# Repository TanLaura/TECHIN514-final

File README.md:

# TECHIN514-final

## Daily Habit Tracker
The device tracks the number of task completed (chips in the collector/sensing device) and show the progress with the stepper gauge needle. The LED light can be on the scale of red to green based on percentage of completion. It relies on the load cell and amplifier to calculate the number of chips of completed tasks and completion rate based on the set goal of the day. The stepper motor gauge and LED will display the progress. The display device also have the option to set the goals.

## Sensor device
The sensor device looks like a bowl overall. There is a load cell and amplifier that read the weight and translate it to voltage. It calculates the percentage of task completion and send the data to display device for further information display.

## Display Device
The outer shape can be varied based on the final PCB shape and size. The diplay has a stepper motor gauge and LED light both shows the completion rate of the task in different forms. It has a reset button and button to adjust the goal of the day.

## Device Communicatioin 

### Component Lists
- [Seeduino ESP32C3](Datasheets/Seeduino ESP32c3.pdf)
- [Load cell](https://www.adafruit.com/product/4541#description): The load cell seems to only have a webpage with product details instead of a datasheet.
- [HX711](Datasheets/adafruit-hx711-24-bit-adc.pdf)
- [Stepper Motor Gauage](Datasheets/stepd-01-data-sheet-1143075.pdf)
- [LED WS2812](Datasheets/WS2812.pdf)

### Potential Component to Add after Discussion 
- A small display screen
- The reset button (and its form)
- A charging circuit?
- Sleep mode?

These are all questions I want to go over with the instruction team to finalize the component list and structure.

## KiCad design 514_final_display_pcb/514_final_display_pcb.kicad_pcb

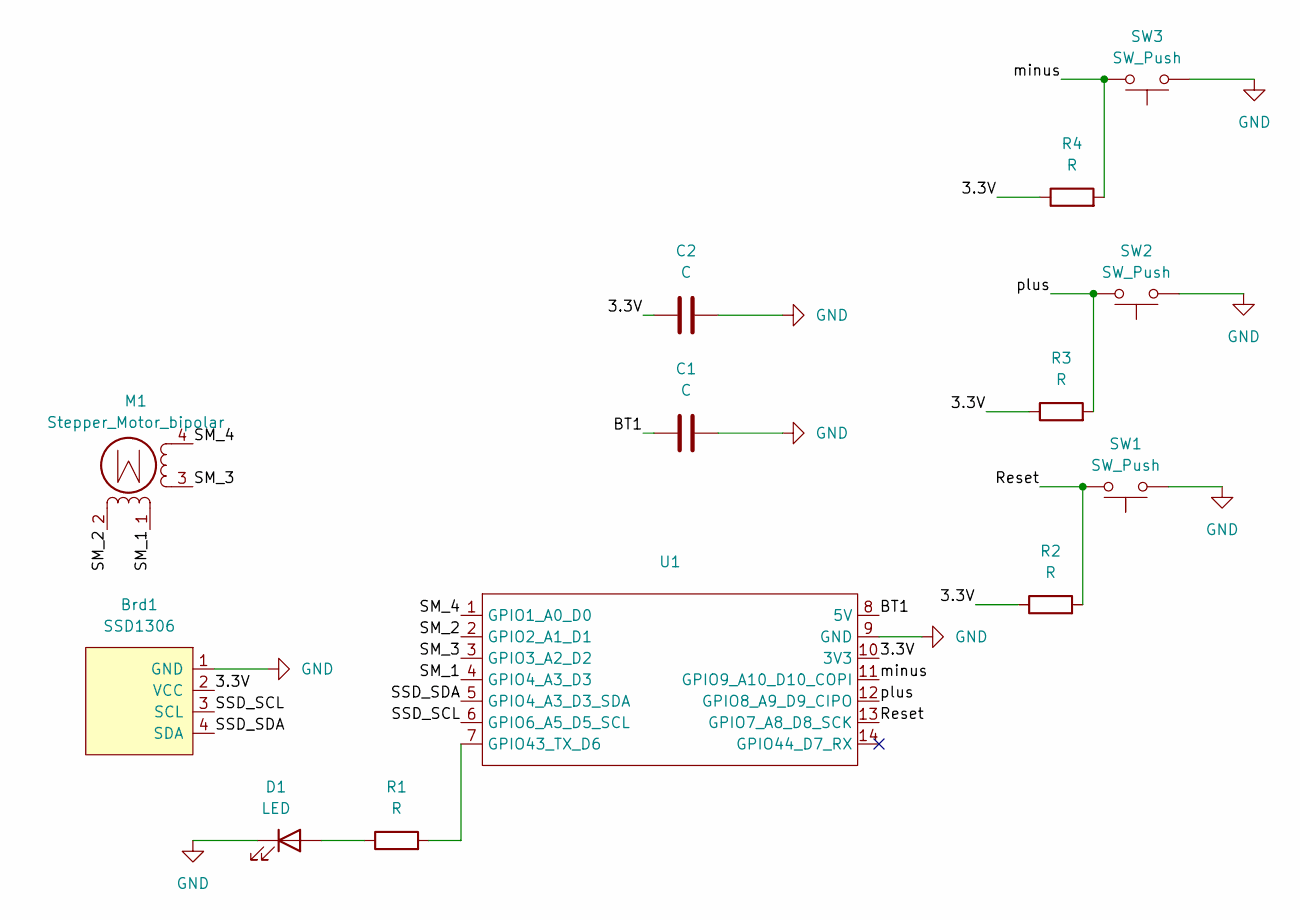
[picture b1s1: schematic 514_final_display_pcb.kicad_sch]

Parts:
Brd1: SSD1306; 128x64OLED
C1, C2: C; C_0805_2012Metric_Pad1.18x1.45mm_HandSolder
D1: LED; LED_D5.0mm
M1: Stepper_Motor_bipolar; x27_stepper_two_holes
R1, R2, R3, R4: R; R_0805_2012Metric_Pad1.20x1.40mm_HandSolder
SW1, SW2, SW3: SW_Push; SW_PUSH_6mm
U1: XIAO_ESP32_SENSE

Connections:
/3.3V: Brd1.2 (VCC), C2.1, R2.1, R3.1, R4.1, U1.10 (3V3)
/BT1: C1.1, U1.8 (5V)
/Reset: R2.2, SW1.2, U1.13 (GPIO7_A8_D8_SCK)
/SM_1: M1.1, U1.4 (GPIO4_A3_D3)
/SM_2: M1.2 (-), U1.2 (GPIO2_A1_D1)
/SM_3: M1.3, U1.3 (GPIO3_A2_D2)
/SM_4: M1.4, U1.1 (GPIO1_A0_D0)
/SSD_SCL: Brd1.3 (SCL), U1.6 (GPIO6_A5_D5_SCL)
/SSD_SDA: Brd1.4 (SDA), U1.5 (GPIO4_A3_D3_SDA)
/minus: R4.2, SW3.2, U1.11 (GPIO9_A10_D10_COPI)
/plus: R3.2, SW2.2, U1.12 (GPIO8_A9_D9_CIPO)
GND: Brd1.1 (GND), C1.2, C2.2, D1.1 (K), SW1.1, SW2.1, SW3.1, U1.9 (GND)
unnamed: D1.2 (A), R1.1
unnamed: R1.2, U1.7 (GPIO43_TX_D6)

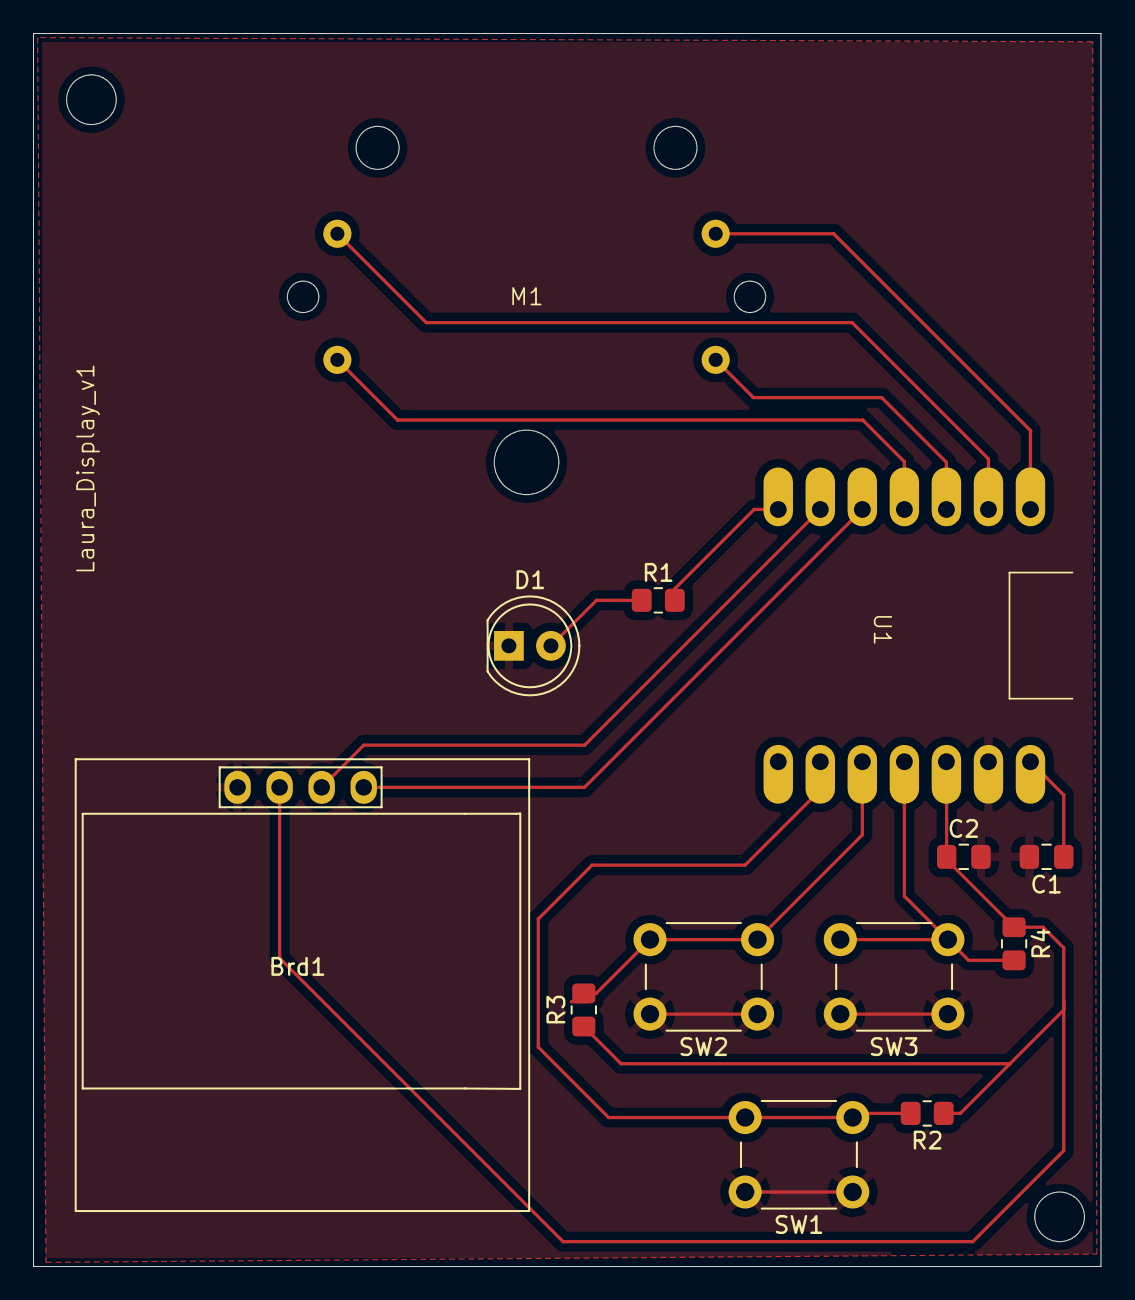
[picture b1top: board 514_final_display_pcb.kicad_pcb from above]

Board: 2 copper layers, 64.5 x 74.5 mm, 13 parts (0 on the bottom side), 14 nets.

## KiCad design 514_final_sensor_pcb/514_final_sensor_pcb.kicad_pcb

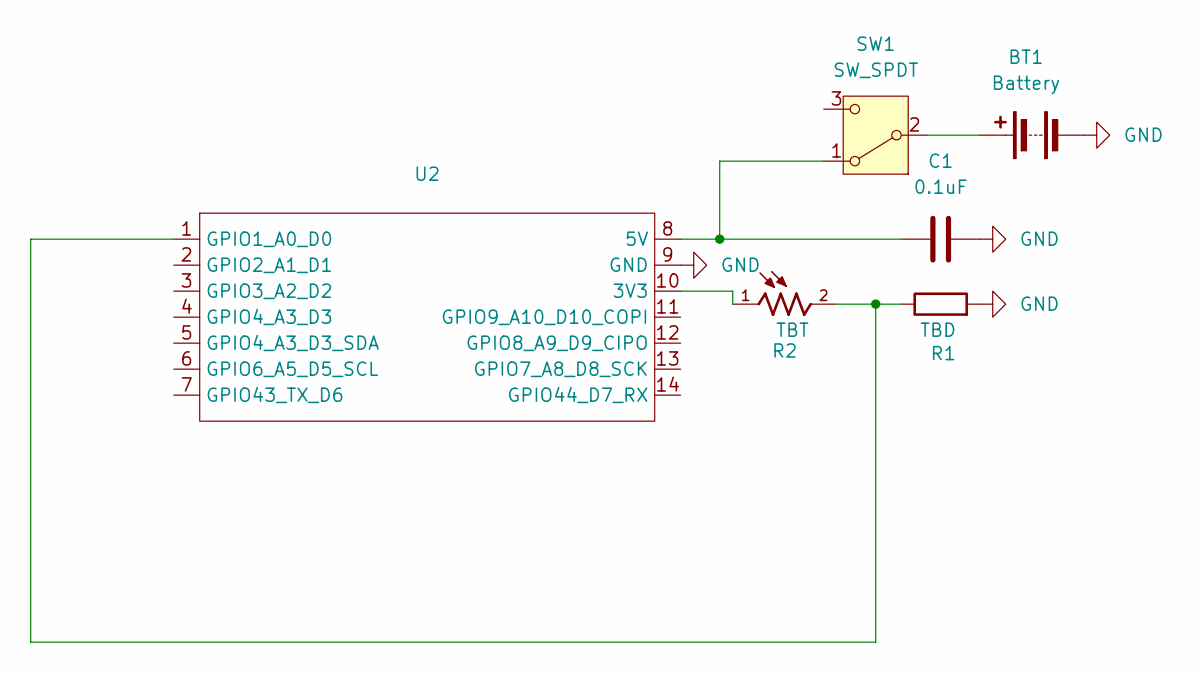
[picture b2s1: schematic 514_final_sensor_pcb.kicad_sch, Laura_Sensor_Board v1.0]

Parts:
BT1: Battery; JST_PH_B2B-PH-K_1x02_P2.00mm_Vertical
C1: 0.1uF; C_0805_2012Metric_Pad1.18x1.45mm_HandSolder
R1: TBD; R_0805_2012Metric_Pad1.20x1.40mm_HandSolder
R2: TBT; PHODET_PDV-P8103; PARTREV 3/30/06
SW1: SW_SPDT; PinHeader_1x03_P2.54mm_Vertical
U2: XIAO_ESP32_SENSE

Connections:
GND: BT1.2 (-), C1.2, R1.2, U2.9 (GND)
unnamed: BT1.1 (+), SW1.2 (B)
unnamed: C1.1, SW1.1 (A), U2.8 (5V)
unnamed: R2.1, U2.10 (3V3)
unnamed: R1.1, R2.2, U2.1 (GPIO1_A0_D0)

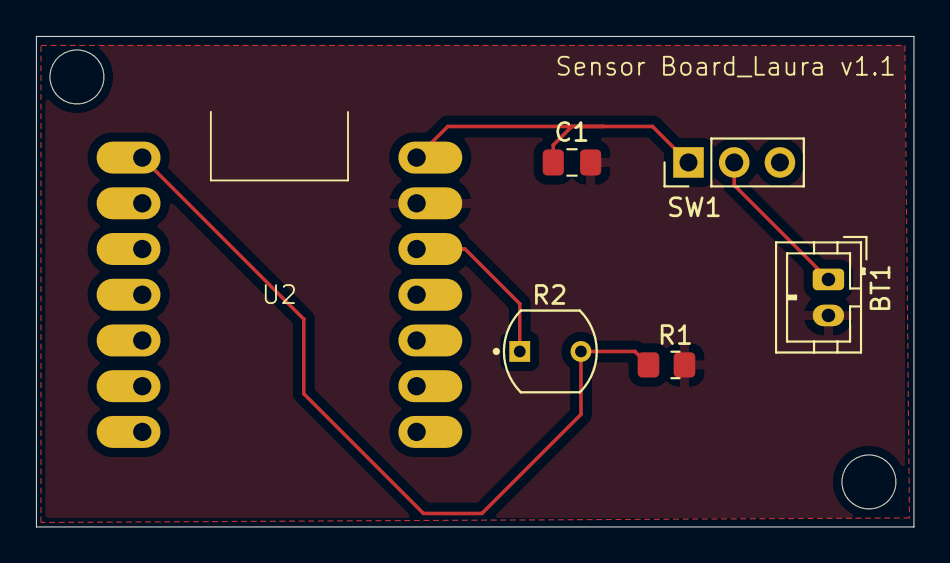
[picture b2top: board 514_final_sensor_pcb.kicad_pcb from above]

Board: 2 copper layers, 48.8 x 27.2 mm, 6 parts (0 on the bottom side), 5 nets.

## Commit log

2025-01-22 system architecture v1
2025-01-22 system architecture v2
2025-01-29 updated datasheet & partial schematic
2025-02-06 sensor pcb v1.0
2025-02-14 battery estimate and datasheet update
2025-02-14 spreadsheet update
2025-03-11 second device
